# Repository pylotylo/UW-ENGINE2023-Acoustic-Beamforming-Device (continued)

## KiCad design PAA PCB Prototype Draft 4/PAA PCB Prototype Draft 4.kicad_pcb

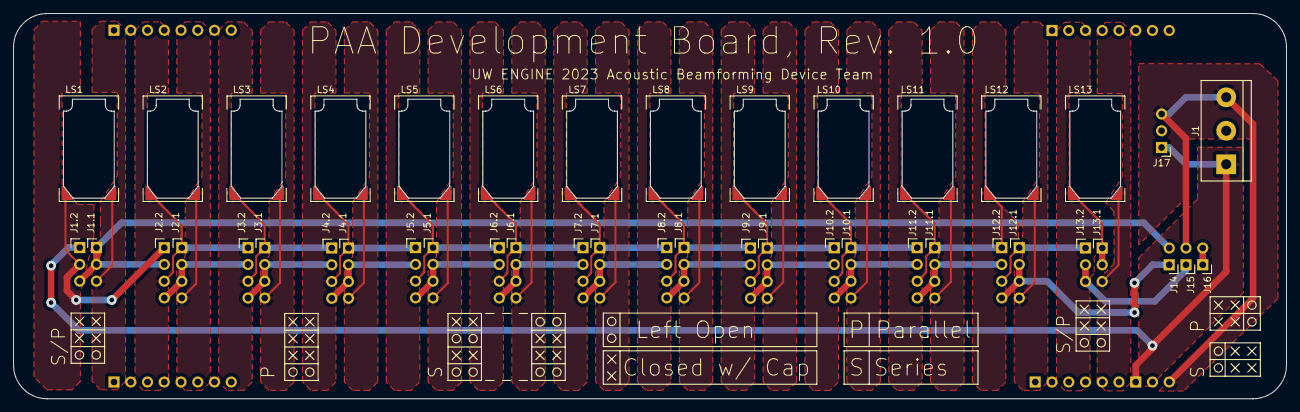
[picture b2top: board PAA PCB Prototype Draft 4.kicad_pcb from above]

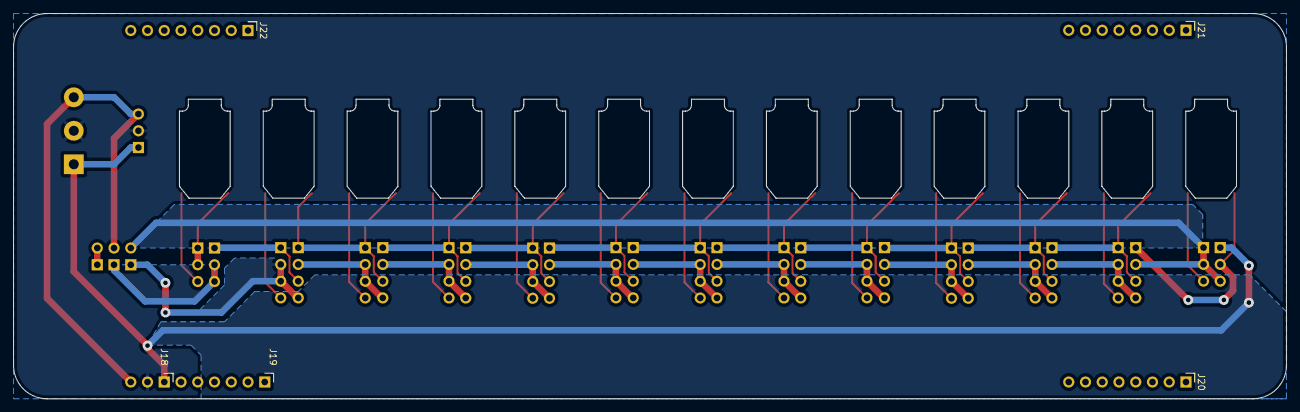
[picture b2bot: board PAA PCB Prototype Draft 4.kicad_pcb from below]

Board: 2 copper layers, 193.0 x 58.4 mm, 49 parts (5 on the bottom side), 43 nets.

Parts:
J1: Screw_Terminal_01x03; TerminalBlock_bornier-3_P5.08mm
J1.1, J1.2, J13.1, J13.2, J17, J18: Conn_01x03_Male; PinHeader_1x03_P2.54mm_Vertical_NoCourtyard
J2.1, J2.2, J3.1, J3.2, J4.1, J4.2, J5.1, J5.2, J6.1, J6.2, J7.1, J7.2, J8.1, J8.2, J9.1, J9.2, J10.1, J10.2, J11.1, J11.2, J12.1, J12.2: Conn_01x04_Male; PinHeader_1x04_P2.54mm_Vertical_NoCourtyard
J14, J15, J16: Conn_01x02_Male; PinHeader_1x02_P2.54mm_Vertical_NoCourtyard
J19: Conn_01x06_Male; PinHeader_1x06_P2.54mm_Vertical_NoCourtyard
J20, J21, J22: Conn_01x08_Male; PinHeader_1x08_P2.54mm_Vertical_NoCourtyard
LS1, LS2, LS3, LS4, LS5, LS6, LS7, LS8, LS9, LS10, LS11, LS12, LS13: Speaker_Ultrasound; Transducer_OWS_081528TA_2

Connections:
/GNDA: J1.2, J17.2, J18.2
A1_B2: J1.2.2, J2.2.1, LS1.1
A2_B3: J2.1.1, J2.2.3, J3.2.1, LS2.1
A3_B4: J3.1.1, J3.2.3, J4.2.1, LS3.1
A4_B5: J4.1.1, J4.2.3, J5.2.1, LS4.1
A5_B6: J5.1.1, J5.2.3, J6.2.1, LS5.1
A6_B7: J6.1.1, J6.2.3, J7.2.1, LS6.1
A7_B8: J7.1.1, J7.2.3, J8.2.1, LS7.1
A8_B9: J8.1.1, J8.2.3, J9.2.1, LS8.1
A9_B10: J9.1.1, J9.2.3, J10.2.1, LS9.1
A10_B11: J10.1.1, J10.2.3, J11.2.1, LS10.1
A11_B12: J11.1.1, J11.2.3, J12.2.1, LS11.1, LS12.1
A12_B13: J12.1.1, J12.2.3, J13.2.1
A13: J13.1.1, J13.1.2, LS13.1
C1_D2: J1.1.1, J1.1.2, J1.2.3, J2.2.2, J14.2
C2_D3: J2.1.2, J2.1.3, J2.2.4, J3.2.2
C3_D4: J3.1.2, J3.1.3, J3.2.4, J4.2.2
C4_D5: J4.1.2, J4.1.3, J4.2.4, J5.2.2
C5_D6: J5.1.2, J5.1.3, J5.2.4, J6.2.2
C6_D7: J6.1.2, J6.1.3, J6.2.4, J7.2.2
C7_D8: J7.1.2, J7.1.3, J7.2.4, J8.2.2
C8_D9: J8.1.2, J8.1.3, J8.2.4, J9.2.2
C9_D10: J9.1.2, J9.1.3, J9.2.4, J10.2.2
C10_D11: J10.1.2, J10.1.3, J10.2.4, J11.2.2
C11_D12: J11.1.2, J11.1.3, J11.2.4, J12.2.2
C12_D13: J12.1.2, J12.1.3, J12.2.4, J14.1
C13: J13.2.2, J13.2.3, J15.1
E_LS1: J1.1.3, LS1.2
E_LS2: J2.1.4, LS2.2
E_LS3: J3.1.4, LS3.2
E_LS4: J4.1.4, LS4.2
E_LS5: J5.1.4, LS5.2
E_LS6: J6.1.4, LS6.2
E_LS7: J7.1.4, LS7.2
E_LS8: J8.1.4, LS8.2
E_LS9: J9.1.4, LS9.2
E_LS10: J10.1.4, LS10.2
E_LS11: J11.1.4, LS11.2
E_LS12: J12.1.4, LS12.2
E_LS13: J13.1.3, LS13.2
Serial_Line: J16.1, J16.2
VinN: J1.3, J15.2, J17.3, J18.3
VinP_B1: J1.1, J1.2.1, J17.1, J18.1

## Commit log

2023-02-16 Add files via upload
    This is a modified version of the TSSOP-48_8x12.5_P0.5mm footprint from the Kicad footprint library. I changed the sizing and spacing of the solder pads in accordance with the PCM1690 datasheet, and 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
2023-02-16 Add files via upload
    This is my first draft of the PCM1690 DAC breakout board. There are a couple notable issues. 1) I used the incorrect footprint, we could update this with the new PCM1690 footprint if we want to order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
2023-02-16 Add files via upload
    This is an incomplete draft, I was experimenting with routing options. I've uploaded this here in case anyone wants to use this draft as a reference.
2023-02-16 Add files via upload
    Draft 3 includes some onboard power-supply decoupling capacitors. Based on figure 41, on page 37 of the PCM1690 datasheet, I placed capacitors C1-C3 in this layout. C4-C6 are electrolytic capacitors,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
    There are a couple issues to fix in this draft. 1) The filled zone for the copper ground pour is not showing up when I try to display it. I followed on online tutorial for adding copper pours, I'm no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
2023-02-16 Add files via upload
    This was an early draft of a breakout board for the TLE2144MDW opamp. Its an incomplete draft, we may revisit it but we've since found other opamp ICs that may be better suited for our needs.
